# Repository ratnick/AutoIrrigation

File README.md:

*AUTONOMOUS CLOUD BASED IRRIGATION SYSTEM*

Pitch
=====

Autonomous watering system based on Arduino WEMOS D1 mini, controlled via
Android app through Firebase cloud. PCB design. Case designed and 3D printed.
Key features: Wifi multi-hotspot, Timed Deep sleep / wake-up, persistent memory
in sync with cloud, multiplexing of analogue inputs, Secure Cloud communication.
Updated to also support an MQ-7 CO monitor (https://www.instructables.com/id/Arduino-CO-Monitor-Using-MQ-7-Sensor/).

Table of contents
=================

[1 Pitch 1](#_Toc28007739)

[2 Table of contents 1](#table-of-contents)

[3 Purpose & Description 1](#purpose-description)

[4 Overall Design drivers 1](#overall-design-drivers)

[5 What you will need to get going…and done.
1](#what-you-will-need-to-get-goingand-done.)

[6 System overview 1](#system-overview)

[7 Hardware & PCB 1](#hardware-pcb)

[8 Data flow & global data structure 1](#data-flow-global-data-structure)

[9 Google Firebase Cloud 1](#google-firebase-cloud)

[10 Arduino control software 1](#arduino-control-software)

[11 Android App 1](#android-app)

[12 Cross-platform: Adding new fields in database
1](#cross-platform-adding-new-fields-in-database)

[13 3D printed case 1](#d-printed-case)

[14 Physical Water supply 1](#physical-water-supply)

[15 Connecting it all 1](#connecting-it-all)

[16 Daily use, installation, tuning 1](#daily-use-installation-tuning)

[17 Appendix A - Hardware & PCB version 6.0 - not tested
1](#appendix-a---hardware-pcb-version-6.0---not-tested)

[18 Log History 1](#log-history)

Purpose & Description
=====================

Key use case: I wanted to have an autonomous watering system for outdoor
watering on a city terrasse with the following main requirements:

-   Easy installation:

    -   No wires or cabling

    -   A low-pressure thin water tube to each water station

-   Easy use

    -   No maintenance or battery exchange

    -   Monitoring and control from app

    -   Can run autonomously for at least 3 weeks (during a holiday)

-   Easy scale

    -   Low price per unit

    -   Easy assembly

    -   Reproducible

Figur 1. The finished unit. Ready to plug into the soil.

Figur . Same unit - disassembled

Figur 3. Close-up of the PCB

Figur . The Android app

Overall Design drivers
======================

Based on the key use case, the following was decided up front as system
components:

-   Power supply: Solar panel to power a Li-Ion battery cell.

-   Low water pressure to enable

    -   Thin water hoses (prettier, easy installation, less risk of high water
        spillage if hose breaks).

    -   Solenoid valve with low power consumption.

-   Arduino WeMos D1 Mini

    -   Wifi enabled

    -   Low power

    -   Just enough I/O

    -   Cheap

    -   Small

    -   Large community knowledge

    -   Had already experience with these

-   Cloud based + App

    -   No need for device to be constant online (saves power, gives autonomy)

    -   Collect of telemetry when system online

    -   Enables monitoring and control of device (via app) via internet without
        device being online (commands stored in Cloud)

-   Own 3D printed case

    -   Smallest and cheapest solution…and most fun.

-   Android app

    -   I have an Android phone + tablet

    -   Probably easiest to integrate with a Google Cloud

What you will need to get going…and done.
=========================================

Just to give an indication of the knowledge needed: I am electronics engineer
from 91, and have not been coding professionally since 2000. Besides what I did
on my study, I have never made electronic circuits, no cloud coding, no 3D
modelling, no Android. Except the actual programming, I learned it all through
this and a couple of other projects. So it is not really that advanced - just
get going.

Apart from that, you will need:

-   Some hardware - but not a lot:

    -   Electronics hardware, mainly WeMos D1 mini, a solar panel, and a few
        other components. Details found below.

    -   Water pressure reduction + water hose. Details found below.

-   3D printer + filament. Details below.

-   Soldering tools. Advanced tools not needed.

-   Multimeter is always good.

-   Total cost is less than 15USD per unit, depending on who your “hardware
    pusher is. I am using Aliexpress.

-   Knowledge of

    -   Visual Studio + how to set it up andwork around problems in confurations
        etc.

    -   How to code for Arduino. Of course this works, but you may want to
        modify.

    -   Android SDK + coding in Android.

    -   Autodesk Fusion 360 for 3D models (well - you only need this if you want
        to modify the models).

    -   Google Firebase - step-by-step tutorial included, but again. You
        probably do not want just to clone.

    -   KiCAD knowledge is fine. I started from scratch, and it is fairly
        simple.

    -   Git. Everything is stored on GITHub.

In brieft, you should (details in each section):

1.  Purchase all material.

2.  Download all code, 3D models, documentation and more from GITHub. On top of
    the code, Ive uploaded real source of e.g. the 3D files (and not just the
    printable files), and all the relevant KiCAD files.  
    At least - that was my intent. If something is missing, let me know.

3.  Install the needed tools. You want to find out up front, if there are
    problems here.

4.  Get the PCB ordered - there is some delivery time on this. Gerber files and
    link included (along with source files).

5.  See if everything compiles and installs.

6.  3D print the case. STL files included (along with source files).

7.  Create the firebase account.

8.  When hardware is received, try to install the Arduino/WEMOS software on the
    bare D1 mini. It should at least start and connect to your wifi.

9.  Create and run the Android app. It is actually not needed to test, except if
    you want to delete logs and telemetry. It is also the only way to get a
    graph of the data.

10. When PCB is received, mount all the components.

11. Install the “golden water pressure reducer.

12. Install the water hoses, turn on the water and enjoy a beer.

System overview
===============

Figur . System overview

Hardware & PCB
==============

Tools
-----

1.  All hardware and PCB is designed using KiCAD. Files are found in the GIT
    file.

**Project file: “irrigation v5.2.pro**

NOTE: At the time of writing, I have made a version 6.0 which has not yet been
PCB printed and tested. That can be found in appendix.

Version 5.2 has been in “production for one summer and works fine. Version 6.0
is optimizing the power conversions, which was a bit cumbersome in 5.2. There
are no changes affecting software.

Overview
--------

Figur . Hardware overview.

1.  The hardware modules are all on same PCB, except:

2.  Solar panel

3.  Soil moisture probe

4.  The valve and valve driver (which is a 5V =\> 12V converter). Valve + driver
    has it is own 3D printed case to facilitate that it is stuck in the soil a
    bit away from the probe.

5.  The Lithium battery and the solar panel are both attached to the charge
    unit, which then makes sure to charge the battery whenever possible +
    provides 5V output power for the device.

Components
----------

Figur 7. All components. (only 1 PCB is used). (soil sensor missing)

File: irrigation v5.3.html (edited)

| Ref       | Qnty | Value        | Part                               | Link                                                                                                                                                                                                                                                                                                 | Description                                                                           |
|-----------|------|--------------|------------------------------------|------------------------------------------------------------------------------------------------------------------------------------------------------------------------------------------------------------------------------------------------------------------------------------------------------|---------------------------------------------------------------------------------------|
| J1        | 1    | Sol          | Connector:Conn_01x02_Female        | \~                                                                                                                                                                                                                                                                                                   | Generic connector, single row, 01x02, script generated                                |
| J2        | 1    | Soil sensor  | Connector:Conn_01x03_Female        | \~                                                                                                                                                                                                                                                                                                   | Generic connector, single row, 01x03, script generated                                |
| J3        | 1    | Valve        | Connector:Conn_01x02_Female        | \~                                                                                                                                                                                                                                                                                                   | Generic connector, single row, 01x02, script generated                                |
| J4        | 1    | Batt         | Connector:Conn_01x02_Female        | \~                                                                                                                                                                                                                                                                                                   | Generic connector, single row, 01x02, script generated                                |
| J5        | 1    | Spare conn.  | Connector:Conn_01x03_Female        | \~                                                                                                                                                                                                                                                                                                   | Generic connector, single row, 01x03, script generated                                |
| Opto1     | 1    | PC817        | Isolator:PC817                     | <https://www.aliexpress.com/item/Free-Shipping-20pcs-lot-PC817C-PC817-EL817-EL817C-DIP-4-817-transistor-output-optocoupler/2040307423.html>                                                                                                                                                          | DC Optocoupler, Vce 35V, CTR 50-300%, DIP4                                            |
| Q1        | 1    | TIP120       | Transistor_BJT:TIP120              | <https://www.aliexpress.com/item/10PCS-TIP102-TIP120-TIP122-TIP127-TIP142-TIP147-LM317T-IRF3205-Transistor-TIP142T-TIP147T/32868103655.html>                                                                                                                                                         | 5A Ic, 60V Vce, Silicon Darlington Power NPN Transistor, TO-220                       |
| R1        | 1    | 100k         | Device:R                           | \~                                                                                                                                                                                                                                                                                                   | Resistor                                                                              |
| R2        | 1    | 5k           | Device:R                           | \~                                                                                                                                                                                                                                                                                                   | Resistor                                                                              |
| Not shown | 1    | SOIL_SENSOR  | SOIL_SENSOR                        | <https://www.aliexpress.com/item/32832538686.html?spm=a2g0o.productlist.0.0.2a5e131byRhwW0&algo_pvid=8fd1c964-4797-471f-8f57-d15732072438&algo_expid=8fd1c964-4797-471f-8f57-d15732072438-1&btsid=a322b86a-1375-41a4-9e58-6b25d2700253&ws_ab_test=searchweb0_0,searchweb201602_3,searchweb201603_53> | Capacitive soil moisture sensor                                                       |
| SW1       | 1    | ON/OFF       | Switch:SW_SPST                     |                                                                                                                                                                                                                                                                                                      | Single Pole Single Throw (SPST) switch                                                |
| SW2       | 1    | flash        | Switch:SW_Push_Open                |                                                                                                                                                                                                                                                                                                      | Push button switch, push-to-open, generic, two pins                                   |
| U2        | 1    | WeMos_mini   | wemos_mini:WeMos_mini              | <https://www.aliexpress.com/item/ESP8266-ESP-12-ESP-12F-CH340G-CH340-V2-USB-WeMos-D1-Mini-WIFI-Development-Board-D1/32633763949.html>                                                                                                                                                                | WeMos D1 mini                                                                         |
| U4        | 2    | J5019        | NNR-lib:J5019                      | <https://www.aliexpress.com/item/Lithium-Li-ion-18650-3-7V-4-2V-Battery-Charger-Board-DC-DC-Step-Up-Boost/32901921699.html>                                                                                                                                                                          | J5019 Lithium Li-ion 18650 3.7V 4.2V Battery Charger Board DC-DC Step Up Boost Module |
| U5        | 1    | CD4052B      | Analog_Switch:CD4052B              | <https://www.aliexpress.com/item/Free-shippin-10pcs-lot-CD74HC4052E-CD74HC4052-74HC4052-DIP16-Switches-new-original/32549841035.html>                                                                                                                                                                | CMOS double 4-channel analog multiplexer/demultiplexer, TSSOP-16/DIP-16/SOIC-16       |
| bat_18650 | 1    | Battery_Cell | Device:Battery_Cell                | 18650 battery cell                                                                                                                                                                                                                                                                                   |                                                                                       |
| Not shown | 1    | valve        | 12V Normally closed solenoid valve | <https://www.aliexpress.com/item/32850727204.html>                                                                                                                                                                                                                                                   |                                                                                       |
| Not shown | 1    | Solar panel  |                                    |                                                                                                                                                                                                                                                                                                      |                                                                                       |

Schematics
----------

File: irrigation v5.3.sch

Figur . Schematics.

PCB layout
----------

Supplier: <https://firstpcb.com/>

File: irrigation v5.3.kicad_pcb

Figur . PCB layout.

Considerations & Notes
----------------------

If this should be made significantly smaller, the way is first to get rid of all
the boards, and use only the components. This is however a “fair amount of work,
and deemed not worth the effort.

Export PCB for print
--------------------

### Export to Gerber files

Result should be the following set of files:

File -\> Plot

Note: It may not be the exact correct values set below.

Drill holes:

Data flow & global data structure
=================================

Note: Firebase is a JSON database, meaning that it is NOT structured in tables
(like a relational database is).

System Data Flow
----------------

Data structure
--------------

| Table                      | Field name (in Arduino code) | JSON name (Firebase and Android)        | Type    | Notes / usage                                                                                                                                                                                                                                                                                |
|----------------------------|------------------------------|-----------------------------------------|---------|----------------------------------------------------------------------------------------------------------------------------------------------------------------------------------------------------------------------------------------------------------------------------------------------|
| **Irrdevice**              |                              |                                         |         | **(one child per device)**                                                                                                                                                                                                                                                                   |
| **metadata**               |                              |                                         |         | **(Semi-static configuration, can be updated runtime)**                                                                                                                                                                                                                                      |
|                            | macAddr                      | mac                                     | String  | (not updatable, used as unique device key)                                                                                                                                                                                                                                                   |
|                            | location                     | loc                                     | String  | Physical location, e.g. “ved gasbrænderen                                                                                                                                                                                                                                                    |
|                            | deviceID                     | device                                  | String  | Hardcoded to device model identifier, PCB version etc                                                                                                                                                                                                                                        |
|                            | sensorType                   | sensor type                             | String  | What sensor type is used (for future scaling to other kinds of sensors)                                                                                                                                                                                                                      |
|                            | hardware                     | hw                                      | String  | Which hardware is used                                                                                                                                                                                                                                                                       |
|                            | softwareVersion              | sw                                      | String  | Software name and compile time                                                                                                                                                                                                                                                               |
| **state**                  |                              |                                         |         | **(updated by device)**                                                                                                                                                                                                                                                                      |
|                            | SSID                         | SSID                                    | String  | Current hotspot                                                                                                                                                                                                                                                                              |
|                            | runOnce                      | runOnce                                 | boolean | Used for debugging and testing                                                                                                                                                                                                                                                               |
|                            | timestamp                    | timestamp                               | long    | ms since 1970.                                                                                                                                                                                                                                                                               |
|                            |                              |                                         |         | Assigned on Firebase server side                                                                                                                                                                                                                                                             |
|                            | sleepCurCycle                | slpCurCyc                               | int     | Current sleep cycle. Between zero and sleepMaxCycles                                                                                                                                                                                                                                         |
|                            | sleepSecondsToSleep          | slpDura                                 | Int     | Seconds See below                                                                                                                                                                                                                                                                            |
|                            | sleepMaxCycles               | slpMxCyc                                | Int     | See below                                                                                                                                                                                                                                                                                    |
| **settings**               |                              |                                         |         | **(can be set runtime by both device and user)**                                                                                                                                                                                                                                             |
|                            | UserUpdate                   | Updated                                 | boolean | Set to true by app or user if user updates any value. Set to false by device when device reads the values.                                                                                                                                                                                   |
|                            | runMode                      | runMode                                 | String  | Soil\|water\|gas\|sensor\|batt\|testhw The device can run in different modes. For normal autonomous watering, use “soil                                                                                                                                                                      |
|                            | valveOpenDuration            | vlvOpen                                 | Int     | Seconds the valve is open (if soil is too dry)                                                                                                                                                                                                                                               |
|                            | soakTime                     | vlvSoak                                 | Int     | Seconds until soil humidity is measured after watering.                                                                                                                                                                                                                                      |
|                            | humLimit                     | humLim                                  | int     | Percentage If humidity \< humlimit, watering will be performed.                                                                                                                                                                                                                              |
|                            | mainLoopDelay                | loopSec                                 | Int     | Seconds to wait between the loop cycles within a single power cycle. The device is awake during this waiting time, so it should not be too long.                                                                                                                                             |
|                            | debugLevel                   | db                                      | int     | 0: only fatal errors are logged to the Firebase log 1-4: more and more logs.                                                                                                                                                                                                                 |
|                            | sleepEnabled                 | slpEnabl                                | boolean | Sleep control parameter.                                                                                                                                                                                                                                                                     |
|                            | totalSecondsToSleep          | totSlp                                  | int     | Sleep control parameter. Total seconds for a sleep cycle. During runtime it is converted to sleepSecondsToSleep and sleepMaxCycles as: sleepMaxCycles = \# of cycles sleeping at max_sleep_duration (hardware number) sleepSecondsToSleep = remainder (last sleep cycles has this duration). |
|                            | wakeupTime[0..3]             | wakeTime0 wakeTime1 wakeTime2 wakeTime3 | String  | Sleep control parameter. HHMMSS 0/1/2 used to set 3 different wake up times per day. 3 is used internally by the device and should not be altered.                                                                                                                                           |
|                            | pauseWakeTime                | pauseTime                               | String  | Sleep control parameter. HHMMSS NOTE: This is not used by the device. Left-over.                                                                                                                                                                                                             |
| **telemetry\_**            |                              |                                         |         | **(last set of values received from device)**                                                                                                                                                                                                                                                |
| **current**                |                              |                                         |         |                                                                                                                                                                                                                                                                                              |
|                            | Vcc                          | Vcc                                     | float   | Measured battery voltage (provided measurement mode is “battery voltage )                                                                                                                                                                                                                    |
|                            | humidity                     | Hum                                     | float   | Measured humidity (provided measurement mode is “humidity )                                                                                                                                                                                                                                  |
|                            | lastAnalogueReading          | lastAnalog                              | int     | Voltage Raw reading (0-1023)                                                                                                                                                                                                                                                                 |
|                            | lastOpenTimestamp            | lastOpen                                | string  | Time when the valve was opened the last time (readable format)                                                                                                                                                                                                                               |
|                            | timestamp                    | timestamp                               | long    | ms since 1970.                                                                                                                                                                                                                                                                               |
|                            |                              |                                         |         | Assigned on Firebase server side                                                                                                                                                                                                                                                             |
|                            | valveState                   | vlvState                                | int     | 0: valve closed, 1: valve open                                                                                                                                                                                                                                                               |
|                            | wifi                         | Wifi                                    | int     | Wifi signal strength in dB                                                                                                                                                                                                                                                                   |
| **telemetry**              |                              |                                         |         | **all values received from device. One entry per timestamp**                                                                                                                                                                                                                                 |
|                            | Same as telemetry_current    |                                         |         |                                                                                                                                                                                                                                                                                              |
| **log**                    |                              |                                         |         | **Real time log (controlled by debugLevel)**                                                                                                                                                                                                                                                 |
|                            | time                         | ts                                      |         |                                                                                                                                                                                                                                                                                              |
|                            | text                         | txt                                     |         |                                                                                                                                                                                                                                                                                              |

Considerations & Notes
----------------------

Google Firebase Cloud
=====================

We use a **Google Firebase Realtime database** as cloud.

Configuration
-------------

1.  <https://console.firebase.google.com/>

2.  Sign up, if needed.

3.  Create a project: Create project

    1.  Name: irrigation

        1.  Note that this name is used in noth Arduino (FIREBASE_HOST)

        2.  Android code (FB_PROJECT_ID) + in app/google-services.json

    2.  ID: irrigation-XXXXXXX

4.  Activate the free trial, if needed

1.  Select Develop =\> Database

2.  Choose to create a new Realtime Database (NOT a Cloud Firestore). Start in
    test mode, but be aware to change later.

    1.  Auth tokens (Database secrets)

Go to Project overview -\> Settings -\> Service accounts

Show and Copy the “secret and insert into Arduino code (typically called
FIREBASE_AUTH)

-   Used in Arduino code in autoirrigation.ino

-   Android code: in app/google-services.json

Links
-----

<https://github.com/GoogleCloudPlatform/google-cloud-iot-arduino>

<https://console.cloud.google.com/home/dashboard?project=cohesive-photon-227011>

<https://console.cloud.google.com/iot/registries?project=cohesive-photon-227011&folder&organizationId&pli=1>

<https://console.cloud.google.com/iot/registries?project=autoirrigation&orgonly=true&supportedpurview=organizationId&walkthrough_tutorial_id=iot_core_quickstart>

Arduino control software
========================

Features
--------

The Arduino software has the following features:

-   Wifi handling

    -   The device will look up a number of predefined hotspots and hook up to
        the first with signal strength above a threshold (to save power, we will
        not hook up to a very weak hotspot).

    -   It will remember the last good hotspot, which allows that the device can
        be moved between e.g. the office and the garden.

-   Deep sleep handling using

    -   Timed wakeup (there are 3 timers per day)

    -   Periodic wake-up: set the time until next wake-up

-   Persistent memory handling

    -   Maintains a mirror of the settings in the cloud. When waking, it reads
        setting, if they have been altered by the user. During runtime, some
        settings may be changed and uploaded to the cloud.

    -   Settings only used internally by device, e.g. last used wifi password
        that worked

-   Multiplexing of analogue input signals

    -   The device can control a multiplexer, allowing to read from several
        sensors. The D1 mini only has one analog port.

    -   This feature also controls the power supply to the sensors (so they only
        use power when measuring).

-   Secure Cloud communication.

    -   There are functions to communicate with Firebase, Azure and Google
        Cloud. Each cloud has it is drawbacks and advantages. This is compile
        time controlled.

Software Components
-------------------

-   Globals (globals, firebasemodel)

    -   Global types and structures

    -   Global names and constants

-   Configuration and main control (autoirrigation.ino)

    -   Compile time configuration

    -   Runtime configuration

    -   Debug configuration

    -   Authentication info

    -   Operating modes (test modes)

    -   Type of device (I am also developing a CO gas sensor; not yet finished)

    -   All communication to cloud (note: there is working software for using
        both Azure and Google Cloud)

-   Power & Sleep (deepsleephandler)

    -   Deep Sleep management

-   Persistent storage (persistentmemory)

    -   Control of the internal persistent memory in the D1. Essentially
        maintaining a mirror of the settings in Firebase.

-   Sensors (analogmux, sensorhandler, soilhumiditysensor, watersensor,
    voltmeter, gassensor)

    -   Multiplexer control

    -   Configuration (different sensors can be used in different ways)

    -   initialization

    -   monitoring

-   Actuators (watervalve, LEDhandler)

    -   Configuration & link to sensors

    -   Initialization

    -   Controlling

-   Wifi mgt (wifi_nnr, wifihandler)

    -   Initialization

    -   connectivity

-   Cloud comm (incl in autoirrigation.ino)

    -   connection

    -   reporting

Tools & setup
-------------

-   Visual Studio Community 2019

-   vMicro extension

-   Create the file wifipasswords.h as described in wifi_nnr.ino. You cant
    compile without it.

-   Install my homemade libraries (also found on my GITHub).

-   Install all needed arduino libraries. Just continue installing until you run
    out of compilation errors 😊

### vMicro extension setup

### Uploading to board - and problems/tips

Note that when uploading there are two things that can tease a bit:

-   Remember to push the small “flash button before flashing. “Unpush the button
    when flashed - otherwise the board will not reset.get if you forget is
    something like “The uploader process failed .

-   If the board is in a long series of sleeps, it will wake up, and immediately
    go back to sleep each time it is reset - until the sleep counter reach it is
    target (zero). You can follow that in the serial output window. Disable this
    by disabling UseSleepMode.

Figure 1. The sleep feature may tease when debugging.

-   If the battery voltage is too low, the board will enter sleep immediately.
    This may provoke a crash dump somehow. Not sure why, but it looks like this.
    If it happens - charge the battery.

Figure 2. Message you get if battery is flat.

Future features:
----------------

-   OTA update. That would really be nice - in particular because the devices
    are placed outdoor in soil.

Android App
===========

I may use wrong terminology here - I am not very familiar with Android. But the
simple app works 😊

Features
--------

-   Hooks up to Firebase and reads + writes data

-   Presents a graph of the data

Overview
--------

-   Main layout:

    -   List of all devices in Firebase with most important data + color code
        for status.

-   Single device layout

    -   Zoom to all relevant settings (yellow) and telemetry of a single device.

    -   Options for purging both telemetry and log data (if there is a lot of
        data, I have not found a way to purge from the WEB interface to
        Firebase).

-   Background service

    -   Maintaining the interface to Firebase + the data

configuration
-------------

Get the google-services.json configuration file from:
<https://support.google.com/firebase/answer/7015592?hl=en>

Tools
-----

-   Android Studio used

Cross-platform: Adding new fields in database
=============================================

Arduino 
--------

Data structure is defined in source code files:

-   Globals.h

-   Persistentmemory.cpp

-   AutoIrrigation.ino

    -   Function CreateTelemetryJson() defines the data transmitted.

-   WaterValve.h

-   WaterSensor.h

Android
-------

-   Source files defining the data structure is under com.vanding.datamodel/

-   FirebaseObject.java encapsulate this data

-   res/layout/content_main.xml and content_single_device.xml contains the
    visual implementation.

3D printed case
===============

Order of design
---------------

1.  Model each hardware component. Placed in separate proejcts.

2.  Import needed

3.  Place them physically as wished

4.  Create base floor. Project spefici markers from the needed components -
    nothing else.

Main components
---------------

F3d files: 3D models of hardware components. This makes it way easier to try out
different layouts.

F3z files: Design of the casing for the irrigation unit. These are importing the
hardware models.

### Main Box for PCB

File: Irrigation unit - Main box (side mounted)

Figur . Main box

Figur 11. Main box with model of PCB and soil sensor.

### Top box with solar panel

File: Irrigation unit - Main box (side mounted)

Figur 12. Ceiling to main box

Figur . ...with solar panel

### Box for valve and valve driver

File: Irrigation unit - valve box

Figur 14. Box for valve and valve driver - seen from the bottom.

Figur ...with components inside

Considerations and notes
------------------------

The principles has been to make it rain resistant by using the fact that “water
do not run upwards 😊 . So it is not water or dust tight, but it can withstand
heavy rain, as long as the device is properly put in the ground.

Tools
-----

-   AutoDesks Fusion360

-   XYZWare Da Vinci Mini w 3D printer

Physical Water supply
=====================

A regular water outlet produce way too much pressure, so reducing the pressure
is essential. It is the basis for

-   reducing risk of water spill in case of malfunctions somewhere

-   reducing power consumption. A higher pressure requires a stronger valve,
    requiring much more power.

-   Having a visually lighter installation, i.e. thinner hoses.

Hardware
--------

### 4/6 mm (inner/outer diameter) flexible water hose.

(link may come later)

### Adjustable water pressure reducer

<https://www.aliexpress.com/item/DN15-Adjustable-Brass-Water-Pressure-Reducing-Regulator-Valve-Internal-and-outer-thread-PN-1-6-and/32964829770.html>

DN15 Adjustable Brass Water Pressure Reducing Regulator Valve Internal and outer
thread PN 1.6 and Pressure Gauge.

-   Material: Brass

-   Connector Size: DN15(G1/2 )

-   Connection Type: Internal /outer Thread

-   Package Contents:

-   1 x Water Pressure Reducing Valve+Wrench+raw material belt

Adjustment
----------

From my memory, water pressure is around 0,1 bar. If it is too high, the valve
will not operate. If too low then it takes too long to water =\> higher power
consumption. An open valve uses \~10W (12V, 1A).

Connecting it all
=================

When done, there are a few pieces that need to be put together.

The main pieces are here:

Daily use, installation, tuning
===============================

Installation 
-------------

The hard work pays off:

-   Install the water tubes

-   Install each device. Give each device a good name - and maybe a sticker on
    the outside, so you can recognize it visually.

-   Make sure the wifi works, check the strength.

-   Check via the app

Appendix A - Hardware & PCB version 6.0 - not tested
====================================================

Version 6.0 is optimizing the power conversions, which was a bit cumbersome in
5.2. There are no changes affecting software.

Components
----------

File: irrigation v6.0.html

**Component Count:**16

| Ref       | Qnty | Value                               | Part                                  | Description                                                                                            | Vendor                                                                                                                                        |
|-----------|------|-------------------------------------|---------------------------------------|--------------------------------------------------------------------------------------------------------|-----------------------------------------------------------------------------------------------------------------------------------------------|
| J1        | 1    | Connector to Solar panel            | Connector:Conn_01x02_Female           | Generic connector, single row, 01x02, script generated (kicad-library-utils/schlib/autogen/connector/) |                                                                                                                                               |
| J2        | 1    | Connector to Batt                   | Connector:Conn_01x02_Female           | Generic connector, single row, 01x02, script generated (kicad-library-utils/schlib/autogen/connector/) |                                                                                                                                               |
| J3, J4    | 2    | Connector to Valve                  | Connector:Conn_01x02_Female           | Generic connector, single row, 01x02, script generated (kicad-library-utils/schlib/autogen/connector/) |                                                                                                                                               |
| J5        | 1    | Connector to Capacitive soil sensor | Connector:Conn_01x03_Female           | Generic connector, single row, 01x03, script generated (kicad-library-utils/schlib/autogen/connector/) |                                                                                                                                               |
| L1        | 1    | 12V Valve                           | Device:Electromagnetic_Actor          | Electromagnetic actor                                                                                  |                                                                                                                                               |
| Opto1     | 1    | PC817                               | Isolator:PC817                        | DC Optocoupler, Vce 35V, CTR 50-300%, DIP4                                                             | <https://www.aliexpress.com/item/Free-Shipping-20pcs-lot-PC817C-PC817-EL817-EL817C-DIP-4-817-transistor-output-optocoupler/2040307423.html>   |
| Q1        | 1    | TIP120                              | Transistor_BJT:TIP120                 | 5A Ic, 60V Vce, Silicon Darlington Power NPN Transistor, TO-220                                        | <https://www.aliexpress.com/item/10PCS-TIP102-TIP120-TIP122-TIP127-TIP142-TIP147-LM317T-IRF3205-Transistor-TIP142T-TIP147T/32868103655.html>  |
| R1        | 1    | 100k                                | Device:R                              | Resistor                                                                                               |                                                                                                                                               |
| R2        | 1    | 5k                                  | Device:R                              | Resistor                                                                                               |                                                                                                                                               |
| SW1       | 1    | flash                               | Switch:SW_Push_Open                   | Push button switch, push-to-open, generic, two pins                                                    |                                                                                                                                               |
| U1        | 1    | J5019                               | NNR-lib:J5019                         | J5019 Lithium Li-ion 18650 3.7V 4.2V Battery Charger Board DC-DC Step Up Boost Module                  | <https://www.aliexpress.com/item/Lithium-Li-ion-18650-3-7V-4-2V-Battery-Charger-Board-DC-DC-Step-Up-Boost/32901921699.html>                   |
| U2        | 1    | 12-24V to 1.8-12V_DCDC_converter    | NNR-lib:12-24V-1.8-12V_DCDC_converter |                                                                                                        | <https://www.aliexpress.com/item/Ultra-Small-Size-DC-DC-Step-Down-Power-Supply-Module-3A-Buck-Converter-Adjustable-1-8V/32880983608.html>     |
| U3        | 1    | WeMos_mini                          | wemos_mini:WeMos_mini                 | WeMos D1 mini R2                                                                                       | <https://www.aliexpress.com/item/ESP8266-ESP-12-ESP-12F-CH340G-CH340-V2-USB-WeMos-D1-Mini-WIFI-Development-Board-D1/32633763949.html>         |
| U4        | 1    | CD4052B                             | Analog_Switch:CD4052B                 | CMOS double 4-channel analog multiplexer/demultiplexer, TSSOP-16/DIP-16/SOIC-16                        | <https://www.aliexpress.com/item/Free-shippin-10pcs-lot-CD74HC4052E-CD74HC4052-74HC4052-DIP16-Switches-new-original/32549841035.html>         |
| bat_1     | 1    | Battery_Cell                        | Device:Battery_Cell                   | Single-cell battery type 18650                                                                         |                                                                                                                                               |
| SOLAR     | 1    | Solar panel                         |                                       |                                                                                                        | <https://www.aliexpress.com/item/ANBES-Solar-Panel-5V-6V-12V-Mini-Solar-System-DIY-For-Battery-Cell-Phone-Chargers-Portable/32848710253.html> |
| Not shown | 1    | valve                               | 12V Normally closed solenoid valve    |                                                                                                        | <https://www.aliexpress.com/item/32850727204.html>                                                                                            |

Schematics
----------

File: irrigation v6.0.sch

PCB layout
----------

File: irrigation v6.0.kicad_pcb

Log History
===========

| Date        | Updates                | Affected modules |
|-------------|------------------------|------------------|
| 15-dec-2019 | Initial public version | all              |
|             |                        |                  |

Save this file as ../README.MD to publish on GitHub with embedded pictures.

Install the plugin <http://www.writage.com/> and export directly from Word.

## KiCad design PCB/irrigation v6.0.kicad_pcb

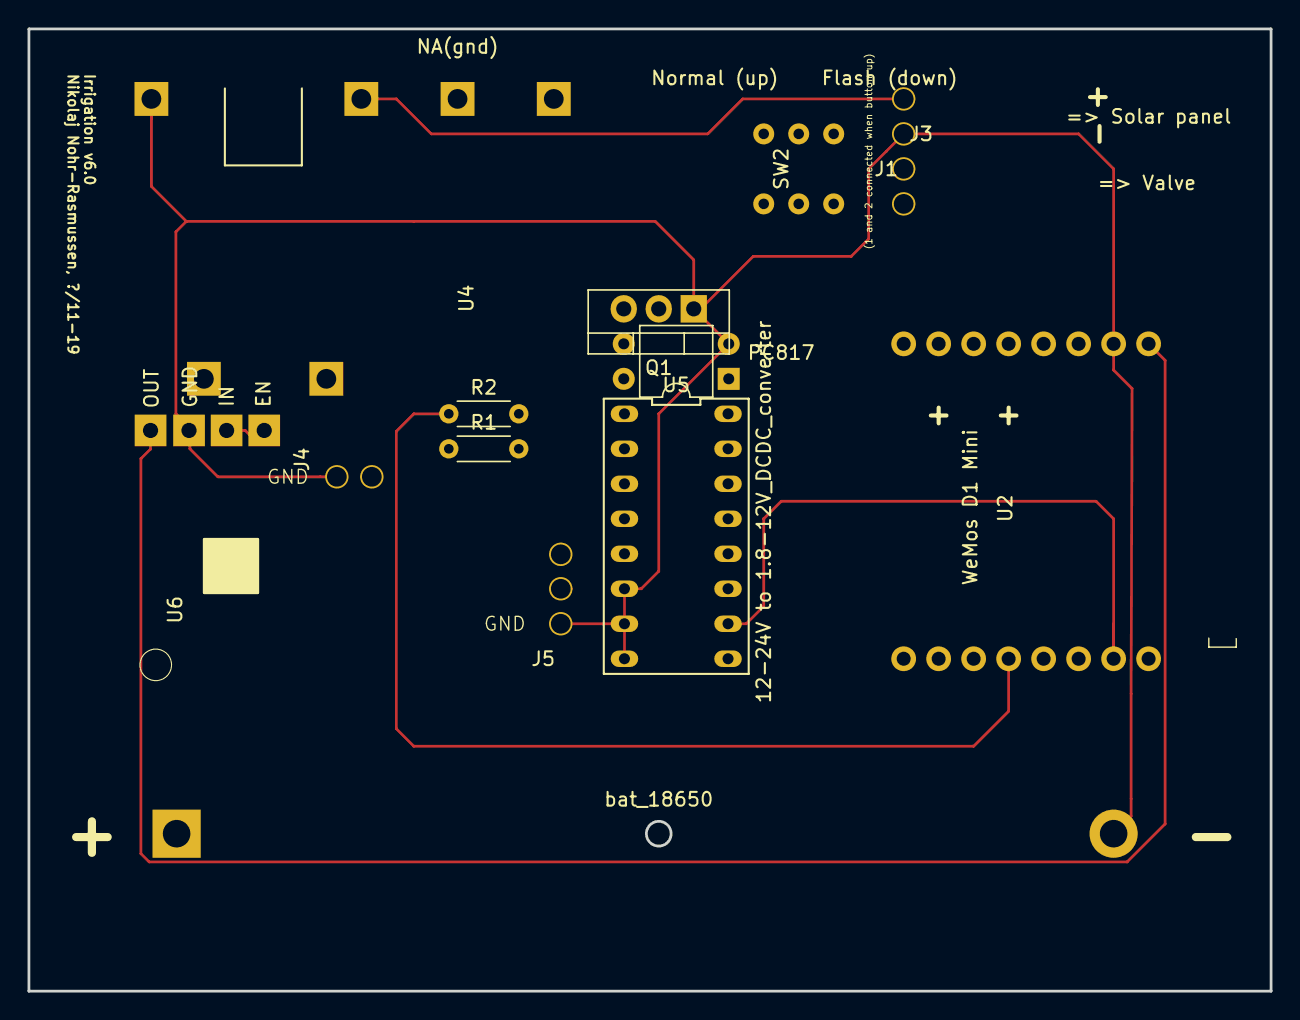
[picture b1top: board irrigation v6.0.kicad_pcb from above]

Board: 6 copper layers, 90.2 x 69.8 mm, 14 parts (0 on the bottom side), 9 nets.

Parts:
J1: => Solar panel; 2p_connector_v2
J3, J4: => Valve; 2p_connector_v2
J5: Capacitive soil sensor; 3p_connector_v1
Opto1: PC817; DIP-4_W7.62mm
Q1: TIP120; TO-220-3_Vertical
R1: 100k; R_Axial_DIN0204_L3.6mm_D1.6mm_P5.08mm_Horizontal
R2: 5k; R_Axial_DIN0204_L3.6mm_D1.6mm_P5.08mm_Horizontal
SW2: flash; onoff_push_button_2x3_pins_v2
U2: 12-24V to 1.8-12V_DCDC_converter; D1_mini_board_v10
U4: CD4052B; J5019_v5
U5: CD4052B; 74HC4052_analogue_mux_v1
U6: 12-24V-1.8-12V_DCDC_converter; 12-5V_DCDC_v2
bat_18650: Battery_Cell; BatteryHolder_MPD_BH-18650-PC2_v4

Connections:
/5V: Opto1.4, U2.1, U6.1
/12V: J3.2, U2.3, U2.4, U6.3, U6.4
GND: J1.1, J5.1, Opto1.2, Q1.3, U2.2, U4.6, U5.6, U5.7, U5.8, U6.2, bat_18650.2
unnamed: J3.1, Q1.2
unnamed: J4.2, bat_18650.1
unnamed: J5.2, Opto1.3, U5.16
unnamed: J5.3, U5.12
unnamed: Q1.1, R2.2
unnamed: R1.2, U5.14

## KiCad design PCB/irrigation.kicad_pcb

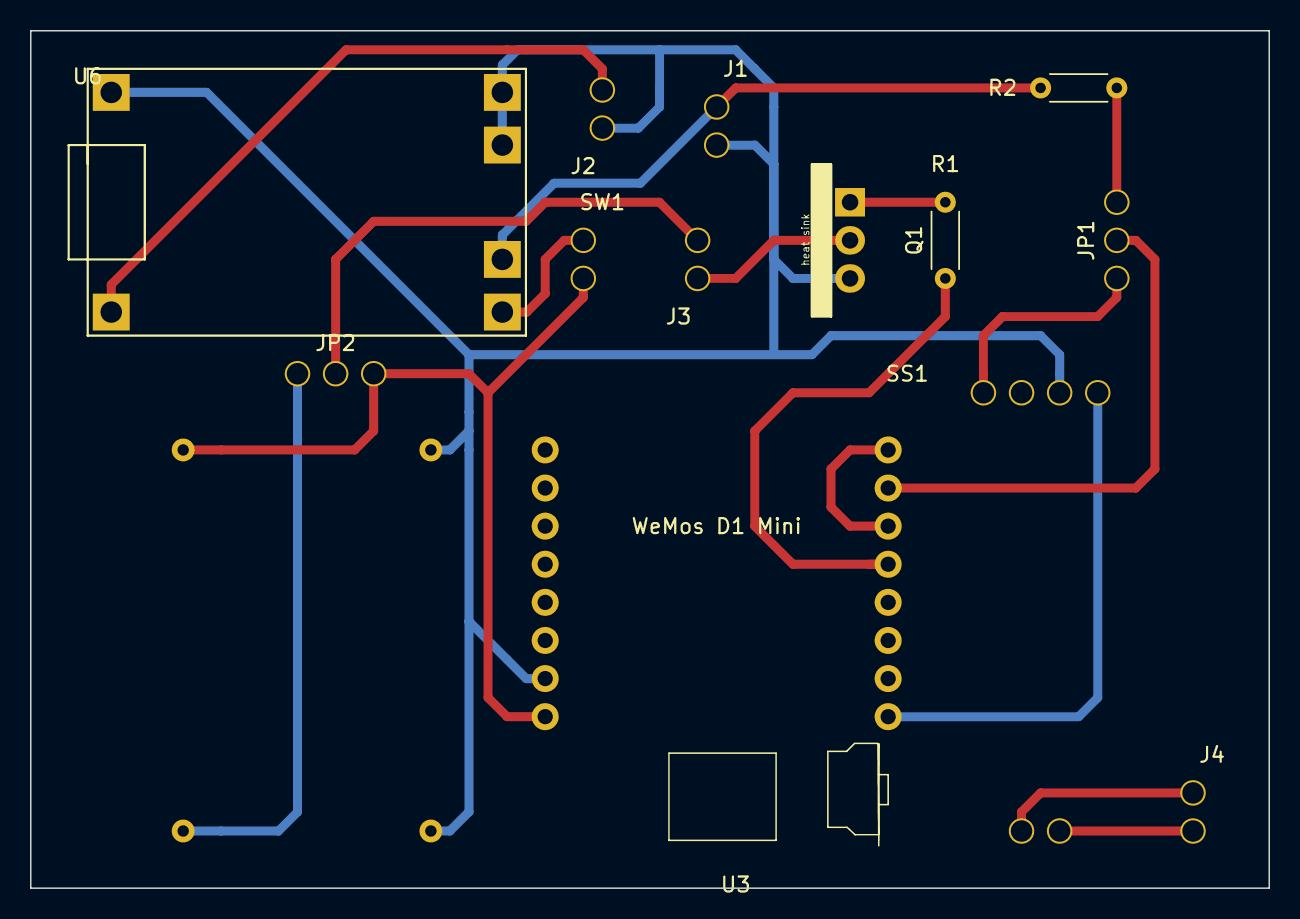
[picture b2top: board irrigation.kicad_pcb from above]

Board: 2 copper layers, 82.6 x 57.1 mm, 14 parts (0 on the bottom side), 17 nets.

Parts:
J1: To Battery; 2p_connector_v2
J2: Solar panel; 2p_connector_v2
J3: Valve; 2p_connector_v2
J4: Soil sensor; 2p_connector_v2
JP1: Humidity/BatteryVolt; 3p_switch_v2
JP2: 5V/12V Valve; 3p_switch_v2
Q1: TIP120; TIP120_v4
R1: 5k; R_Axial_DIN0204_L3.6mm_D1.6mm_P5.08mm_Horizontal
R2: 100k; R_Axial_DIN0204_L3.6mm_D1.6mm_P5.08mm_Horizontal
SS1: SOIL_SENSOR; Soil sensor_v3
SW1: ON/OFF; 2p_connector_v2
U1: 5-12V_DCDC_Converter; 5-12V_DCDCv4
U3: WeMos_mini; D1_mini_board_v4
U6: TP4056; TP4056_v2

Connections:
GND: J1.2, J2.1, Q1.3, SS1.3, U1.3, U1.4, U3.2, U6.1, U6.2, U6.6
unnamed: J1.1, R2.1, U6.3
unnamed: J2.2, U6.5
unnamed: J3.1, Q1.2
unnamed: J3.2, JP2.2
unnamed: J4.1, SS1.5
unnamed: J4.2, SS1.6
unnamed: JP1.1, SS1.1
unnamed: JP1.2, U3.10
unnamed: JP1.3, R2.2
unnamed: JP2.1, U1.1
unnamed: JP2.3, SW1.2, U1.2, U3.1
unnamed: Q1.1, R1.2
unnamed: R1.1, U3.12
unnamed: SS1.4, U3.16
unnamed: SW1.1, U6.4
unnamed: U3.9, U3.11

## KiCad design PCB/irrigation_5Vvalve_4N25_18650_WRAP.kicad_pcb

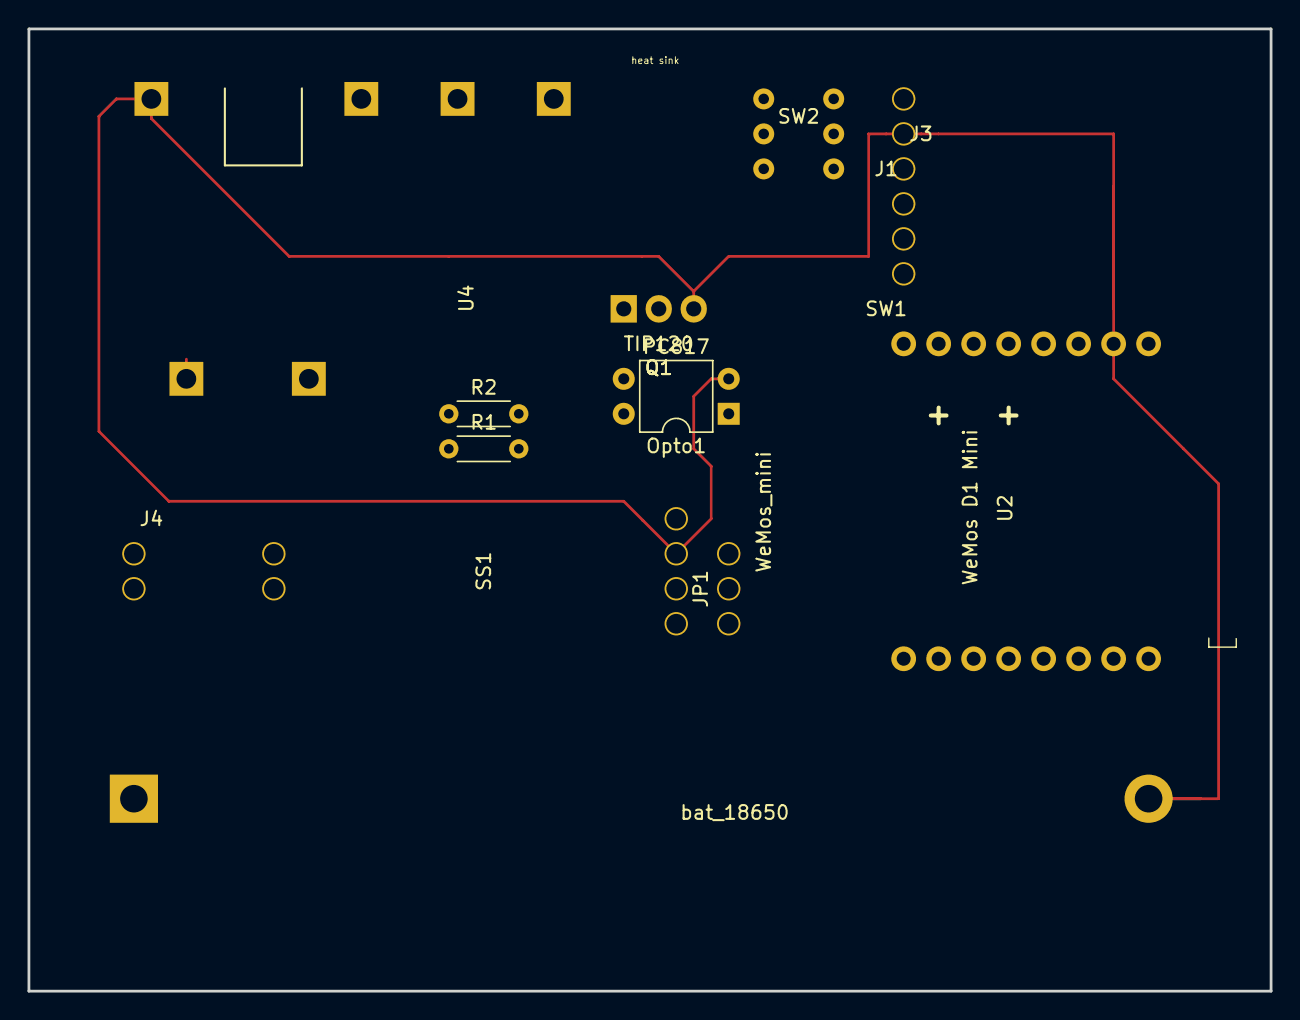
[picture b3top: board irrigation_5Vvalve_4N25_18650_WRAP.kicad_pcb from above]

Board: 6 copper layers, 90.2 x 69.8 mm, 14 parts (0 on the bottom side), 17 nets.

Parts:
J1: Sol; 2p_connector_v2
J3: Valve; 2p_connector_v2
J4: Soil sensor; 2p_connector_v2
JP1: BATT / HUM; 3p_switch_v2
Opto1: PC817; DIP-4_W7.62mm
Q1: TIP120; TIP120_flat_v2
R1: 100k; R_Axial_DIN0204_L3.6mm_D1.6mm_P5.08mm_Horizontal
R2: 5k; R_Axial_DIN0204_L3.6mm_D1.6mm_P5.08mm_Horizontal
SS1: SOIL_SENSOR; Soil sensor_v4
SW1: ON/OFF; 2p_connector_v2
SW2: flash; onoff_push_button_2x3_pins_v2
U2: WeMos_mini; D1_mini_board_v10
U4: J5019; J5019_v4
bat_18650: Battery_Cell; BatteryHolder_MPD_BH-18650-PC2_v2

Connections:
GND: J1.1, Opto1.2, Q1.3, SS1.GND, U2.2, U4.1, U4.2, U4.6, bat_18650.2
unnamed: J1.2, U4.5
unnamed: J3.1, Q1.2
unnamed: J3.2, Opto1.4, SW1.2, U2.1
unnamed: J4.1, SS1.+
unnamed: J4.2, SS1.-
unnamed: JP1.1, SS1.A0
unnamed: JP1.2, U2.10
unnamed: JP1.3, R1.2
unnamed: Opto1.1, U2.6
unnamed: Opto1.3, SS1.VCC
unnamed: Q1.1, R2.2
unnamed: R1.1, U4.3, bat_18650.1
unnamed: R2.1, U2.12
unnamed: SW1.1, U4.4
unnamed: SW2.1, U2.11
unnamed: SW2.2, U2.9

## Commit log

2018-09-23 Add .gitignore and .gitattributes.
2018-09-23 Add project files.
2019-03-21 Arduino side: - Firebase interface including: -- read/write of state for configuring during runtime -- write telemetry -- log -- Device creation - Deep Sleep configurable from Firebase / app - Abilit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
    Android Side
    - Read / write to Firebase
    - Support for multiple devices
    - Graph (timeline)
    - Still missing:
    -- Some actions on added data (changes works fine). Basics works fine.
2019-03-21 Removed unused files (tests, earlier versions etc)
2019-03-21 Added Wiring diagram, layout for wrapping and documentation
2019-04-04 - Changed DeepSleep handling. - Modified Firebase parameters handling Deep Sleep - Added time adjustment to danish summertime (permanently). - Added power down of sensor unit during setup() - Changed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
2019-04-04 Adding files for 3D printing and schematics + PCB/wrap layout
2019-04-04 Updated JSON database layout in Firebase, Arduino and Android. Documented in Word file.
2019-04-05 renamed package from dycodex to ratnick
2019-04-20 Works before Google Firebase interface has been changed (by Google)
2019-04-21 Changed firebase interface library
2019-04-22 Introduced runMode
2019-04-23 enable setting humidity limit from app.
2019-04-23 Change averaging period for battery voltage (from 10 samples to 3)
2019-04-23 upgrade og Android SDK
2019-04-30 Use Deep sleep during longer soak periods
2019-04-30 New feature: Purge telemetry data
2019-04-30 Box for external valve
2019-06-21 Sleep until scheduled time of day. Some started work on gas sensor (not finished)
2019-07-01 - fbDebugLevel included in persistent memory. - Transmit of fbDebugLevel to and from FireBase works.
2019-07-28 LogLinef changed to follow syntak in sprintf(). Logline and Loglinef now taking only char[] as input (i.e. no longer using String). LogLineFB and LogLinefFB introduced to enable logging to Firebase c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
2019-08-01 Logging to Firebase works. Possible to set debug level directly from Firebase.
2019-08-22 - added 4 wakeupTimes - added pausewaketime - Initialize and get+set in persistent memory - send/fetch from Firebase Compiles, but not testet at all
2019-08-24 vcxproj files
2019-08-24 project file
2019-08-24 project files
2019-08-24 Compiles and runs without crashes: - logging to cloud - 4 waketimes (included, but not in use)
2019-08-31 Added wake up at specific time.
2019-09-03 - Unit test of DeepSleepHandler - Corrected some errors. - DeepSleepHandler now works
2019-09-04 insignificant updates to Android app
2019-09-06 DeepSleep: Added adjustment for drifting closk
2019-09-15 Small correction in deep sleep: wait for final sleep loop before measuring
2019-09-20 Fixed: Multiple Vcc lines on graph in app.
2019-10-26 Rewritten android app. Deleting old version.
2019-10-26 Rewritten android app. Committing new version.
2019-10-28 Updates to app: - Refreshing internal database on any change in firebase - purge log and telemetry works
2019-10-28 minor changes
2019-10-30 - option for adjusting Vcc measurement by setting Vmax - option for adjusting Vcc minimum limit before entering sleep
2019-11-12 Bugfix: Not storing totalSleepSecs
2019-11-13 PCB changes: - Simplified power supply (removing Step-up, including step-down)
2019-11-13 Created zip file for new PCB (v6.0)
2019-11-13 minor updates
2019-11-13 PCB version 6.0 ZIP containing the correct version (in case of doubt)
2019-11-17 Minor update to build file
2019-12-08 Android app: - Introduced exit of application when pressing back twice. - minor upgrades of library versions. - Suppression of warning in IrrDevice
2019-12-08 Updating documentation Working on PCB board version 6.0 (only 5V and different power supply circuit)
2019-12-15 Clean-up for making public
2019-12-15 Initial public version.
2019-12-15 Made local passwords private.
2019-12-23 Updated documentation to MarkDown format
2019-12-29 minor update
2020-01-01 temporary work - not working
2020-01-12 Upgraded to latest version (2.7.6) of Firebase-ESP8266 by @Mobitz. Now support for many types of telemetry; defined by the sensors attached (they now produce their own telemetry which is collected by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
2020-01-18 Gas sensor now working on D1 side: - receive JSON via serial port from external sensing device - build telemetry and send it.
2020-02-01 Update of Android app to include a gas sensor device.
2020-02-09 Added detailed graph view in landscape mode
2020-03-28 Added ventilation holes in case
2020-03-28 Bugfix: totslp forgotten in settings in Firebase Changed to soil sensor mode.
2020-03-28 Gradle version update to Android
2020-03-29 Added "soil" as default value for device type Changed debug levels generally.
2020-10-25 Included DHT11 temperature + humidity sensor
2020-10-25 Reorganized compile flags and checked that Irrigation device was still working.
2020-11-02 New 3D files for a small sensor (DHT22) Added a compile_flag header file
2021-01-24 Added one digit to read-out
2021-02-09 Updates to app: - Pull down to refresh - skip wifi strength on entry page
2021-02-09 Bug fix + preparation for OTA update: - replace delay with non-blocking delay
2021-02-09 Autodetect between DHT11 and DHT22 (not sure the library function is working though). Now defaults to DHT22. For DHT22: handling negative temperatures.
2021-02-09 Enabling compilation without Deep Search every time.
2021-02-09 - Cleanup - removed code referring to Google Cloud (not Firebase)
    - Updates to Firebase interface + upgrade og API:
    - Made library for (almost) all direct communication to Firebase
    - Simplified control structure in AutoIrrigation.ino
    - Error fix:
    - Updates to LogLib to handle error when sending "/" or "\" to Firebase log
    - Prepare for OTA update (not fully functional yet):
2021-03-17 Device: - re-adding humidity to sensors (was removed and zeroed)
    App:
    - swapped Humidity ad Wifi between primary and secondary axis for temperature sensors.
    - No display of Wifi anymore for temperature sensors
2021-05-13 small test of an infrared water sensor
2021-10-18 Changes to Android graphs
2021-10-18 Initial distance sensor. Not finished.
2021-10-18 Cleanup in library references
2022-01-02 Use of new version of PersistentMemory to improve Firebase integration. Using v6 (instead of v5) of ArduinoJson library
2022-01-02 Added exception handler for error with inserted timestamp in telemetry.
2022-01-02 Support for new version of Gradle
2022-01-18 Compiles, but some rollbacks of Firebase_PersistentMemory
2022-01-18 LEDHandler => NNR_LEDHandler
2022-01-18 OTALib => NNR_OTAupdate
2022-01-18 WifiLib => NNR_Wifi
2022-01-18 LogLib => NNR_Logging
2022-01-19 PersistentMemory => NNR_PersistentMemory. Does not compile since FirebaseModel.h has not yet been moved around.
2022-01-19 FirebaseLib => NNR_FirebaseDatabase
2022-01-19 Firebase_PersistentMemory => NNR_Firebase_PersistentMemory
2022-03-22 Android App: Dynamic device display. (feb 2022)
    Made on wrong code folder on summer house PC
2022-03-22 These files are maintained in IOT_Devices from now on.
2022-03-22 Update of Android SDK
2022-04-10 Support for wew device type: Pump controller
2022-12-27 Move Firebase base path to v2. New feature: purge every N'th sample New feature: add offset to data
